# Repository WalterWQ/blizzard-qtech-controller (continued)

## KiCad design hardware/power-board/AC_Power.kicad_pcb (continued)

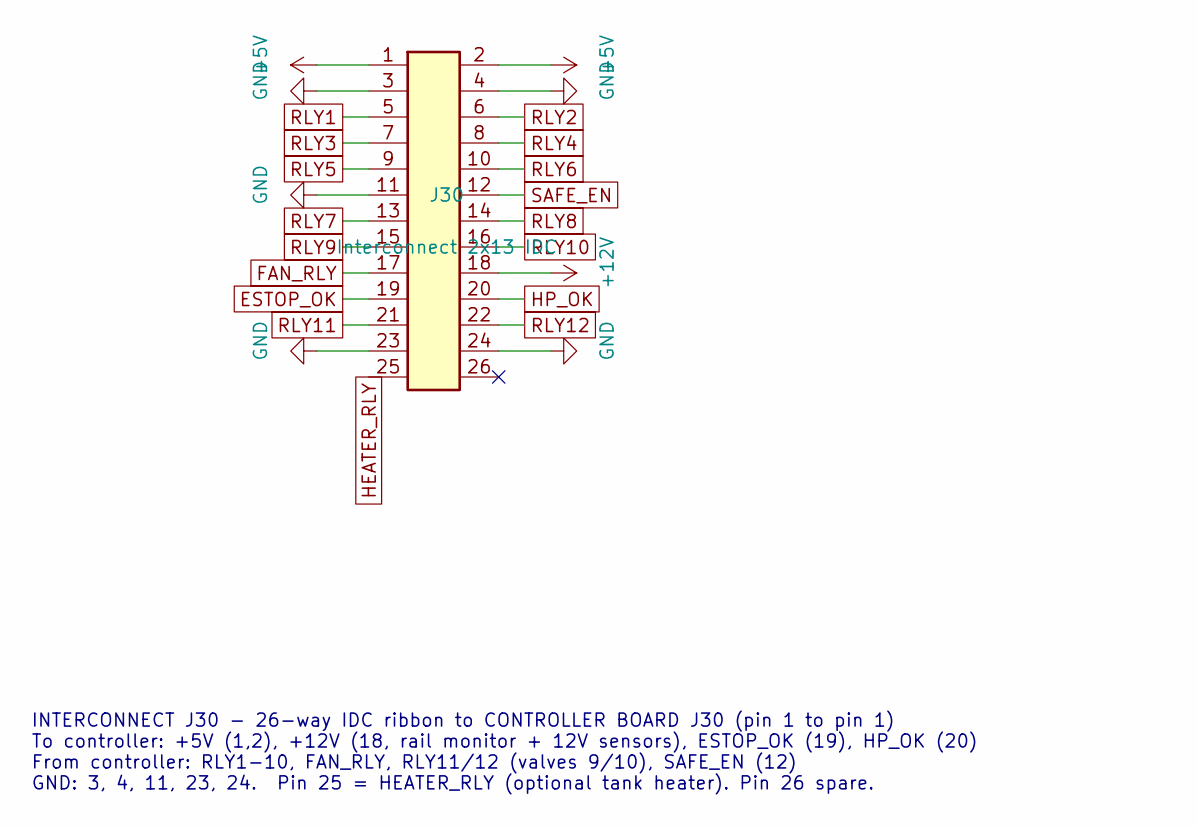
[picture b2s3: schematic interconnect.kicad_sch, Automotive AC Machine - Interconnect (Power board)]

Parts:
J30: Interconnect 2x13 IDC; IDC-Header_2x13_P2.54mm_Vertical

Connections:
+5V: J30.1, J30.2; also elsewhere on the board
+12V: J30.18; also elsewhere on the board
ESTOP_OK: J30.19; also elsewhere on the board
FAN_RLY: J30.17; also elsewhere on the board
GND: J30.3, J30.4, J30.11, J30.23, J30.24; also elsewhere on the board
HEATER_RLY: J30.25; also elsewhere on the board
HP_OK: J30.20; also elsewhere on the board
N_J30.26: J30.26
RLY1: J30.5; also elsewhere on the board
RLY2: J30.6; also elsewhere on the board
RLY3: J30.7; also elsewhere on the board
RLY4: J30.8; also elsewhere on the board
RLY5: J30.9; also elsewhere on the board
RLY6: J30.10; also elsewhere on the board
RLY7: J30.13; also elsewhere on the board
RLY8: J30.14; also elsewhere on the board
RLY9: J30.15; also elsewhere on the board
RLY10: J30.16; also elsewhere on the board
RLY11: J30.21; also elsewhere on the board
RLY12: J30.22; also elsewhere on the board
SAFE_EN: J30.12; also elsewhere on the board

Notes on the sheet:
INTERCONNECT J30 - 26-way IDC ribbon to CONTROLLER BOARD J30 (pin 1 to pin 1) To controller: +5V (1,2), +12V (18, rail monitor + 12V sensors), ESTOP_OK (19), HP_OK (20) From controller: RLY1-10, FAN_RLY, RLY11/12 (valves 9/10), SAFE_EN (12) GND: 3, 4, 11, 23, 24. Pin 25 = HEATER_RLY (optional tank 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

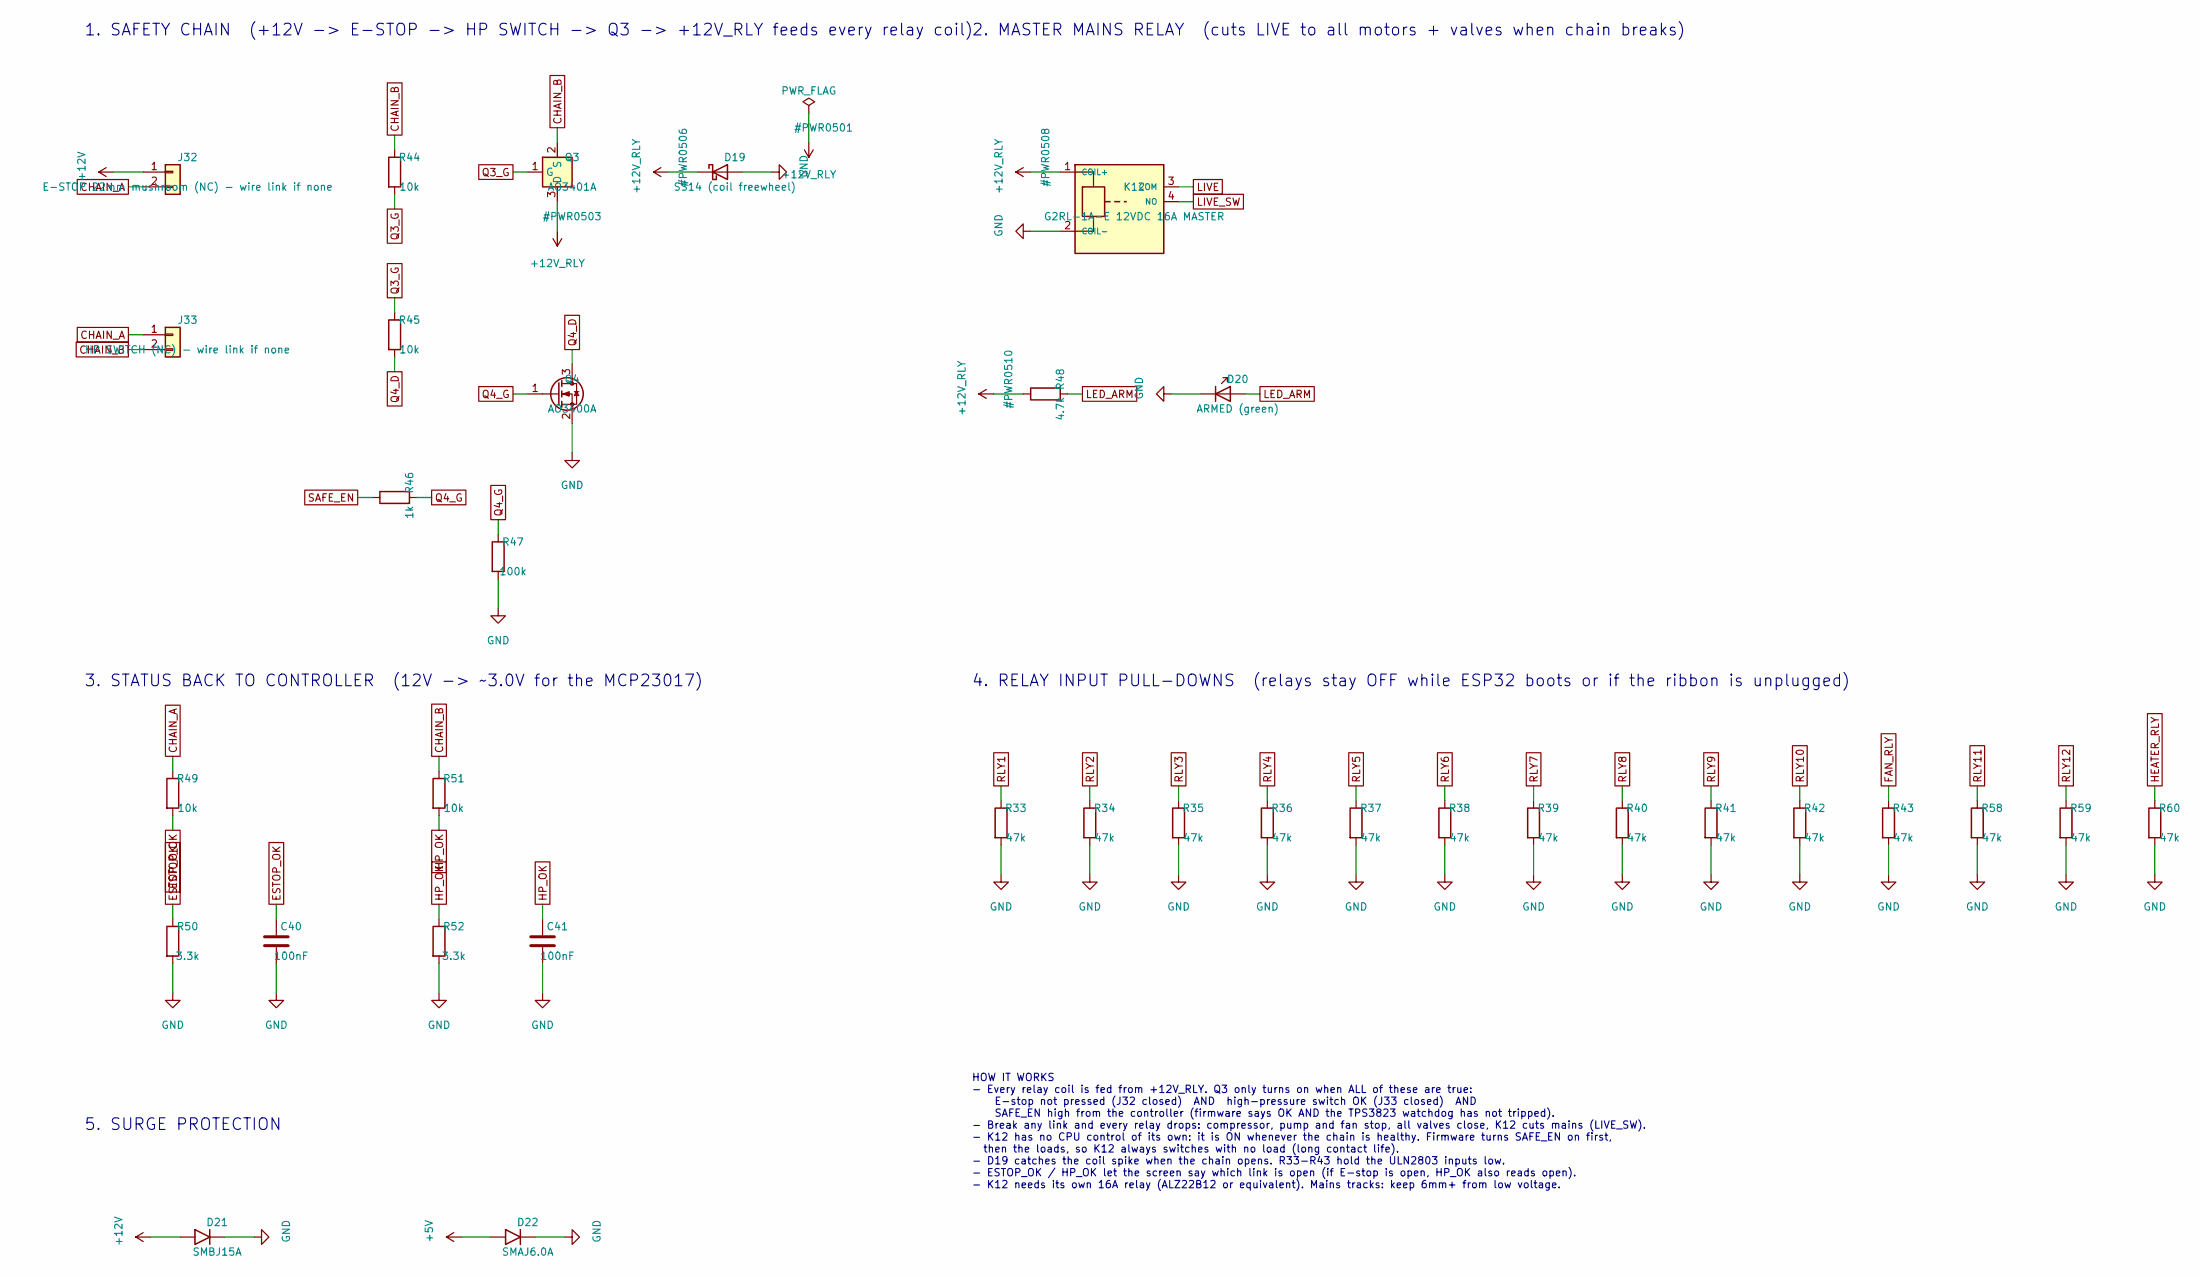
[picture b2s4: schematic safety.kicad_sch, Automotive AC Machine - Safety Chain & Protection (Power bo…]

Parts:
C40, C41: 100nF; C_0805_2012Metric
D19: SS14 (coil freewheel); D_SMA
D20: ARMED (green); LED_0805_2012Metric
D21: SMBJ15A; D_SMB
D22: SMAJ6.0A; D_SMA
J32: E-STOP 22mm mushroom (NC) - wire link if none; TerminalBlock_Phoenix_MKDS-1,5-2-5.08_1x02_P5.08mm_Horizont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
J33: HP SWITCH (NC) - wire link if none; TerminalBlock_Phoenix_MKDS-1,5-2-5.08_1x02_P5.08mm_Horizont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
K12: G2RL-1A-E 12VDC 16A MASTER; Relay_G2RL-1A-E_QT
Q3: AO3401A; SOT-23
Q4: AO3400A; SOT-23
R33, R34, R35, R36, R37, R38, R39, R40, R41, R42, R43, R58, R59, R60: 47k; R_0805_2012Metric
R44, R45, R49, R51: 10k; R_0805_2012Metric
R46: 1k; R_0805_2012Metric
R47: 100k; R_0805_2012Metric
R48: 4.7k; R_0805_2012Metric
R50, R52: 3.3k; R_0805_2012Metric

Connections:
+5V: D22.1 (K); also elsewhere on the board
+12V: D21.1 (K), J32.1; also elsewhere on the board
+12V_RLY: D19.1 (K), K12.1 (COIL+), Q3.3 (D), R48.1; also elsewhere on the board
CHAIN_A: J32.2, J33.1, R49.1
CHAIN_B: J33.2, Q3.2 (S), R44.1, R51.1
ESTOP_OK: C40.1, R49.2, R50.1; also elsewhere on the board
FAN_RLY: R43.1; also elsewhere on the board
GND: C40.2, C41.2, D19.2 (A), D20.1 (K), D21.2 (A), D22.2 (A), K12.2 (COIL-), Q4.2 (S), R33.2, R34.2, R35.2, R36.2, R37.2, R38.2, R39.2, R40.2, R41.2, R42.2, R43.2, R47.2, R50.2, R52.2, R58.2, R59.2, R60.2; also elsewhere on the board
HEATER_RLY: R60.1; also elsewhere on the board
HP_OK: C41.1, R51.2, R52.1; also elsewhere on the board
LED_ARM: D20.2 (A), R48.2
LIVE: K12.3 (COM); also elsewhere on the board
LIVE_SW: K12.4 (NO); also elsewhere on the board
Q3_G: Q3.1 (G), R44.2, R45.1
Q4_D: Q4.3 (D), R45.2
Q4_G: Q4.1 (G), R46.2, R47.1
RLY1: R33.1; also elsewhere on the board
RLY2: R34.1; also elsewhere on the board
RLY3: R35.1; also elsewhere on the board
RLY4: R36.1; also elsewhere on the board
RLY5: R37.1; also elsewhere on the board
RLY6: R38.1; also elsewhere on the board
RLY7: R39.1; also elsewhere on the board
RLY8: R40.1; also elsewhere on the board
RLY9: R41.1; also elsewhere on the board
RLY10: R42.1; also elsewhere on the board
RLY11: R58.1; also elsewhere on the board
RLY12: R59.1; also elsewhere on the board
SAFE_EN: R46.1; also elsewhere on the board

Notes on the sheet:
1. SAFETY CHAIN (+12V -> E-STOP -> HP SWITCH -> Q3 -> +12V_RLY feeds every relay coil)
2. MASTER MAINS RELAY (cuts LIVE to all motors + valves when chain breaks)
3. STATUS BACK TO CONTROLLER (12V -> ~3.0V for the MCP23017)
4. RELAY INPUT PULL-DOWNS (relays stay OFF while ESP32 boots or if the ribbon is unplugged)
5. SURGE PROTECTION
HOW IT WORKS - Every relay coil is fed from +12V_RLY. Q3 only turns on when ALL of these are true: E-stop not pressed (J32 closed) AND high-pressure switch OK (J33 closed) AND SAFE_EN high from the controller (firmware says OK AND the TPS3823 watchdog has not tripped). - Break any link and every re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

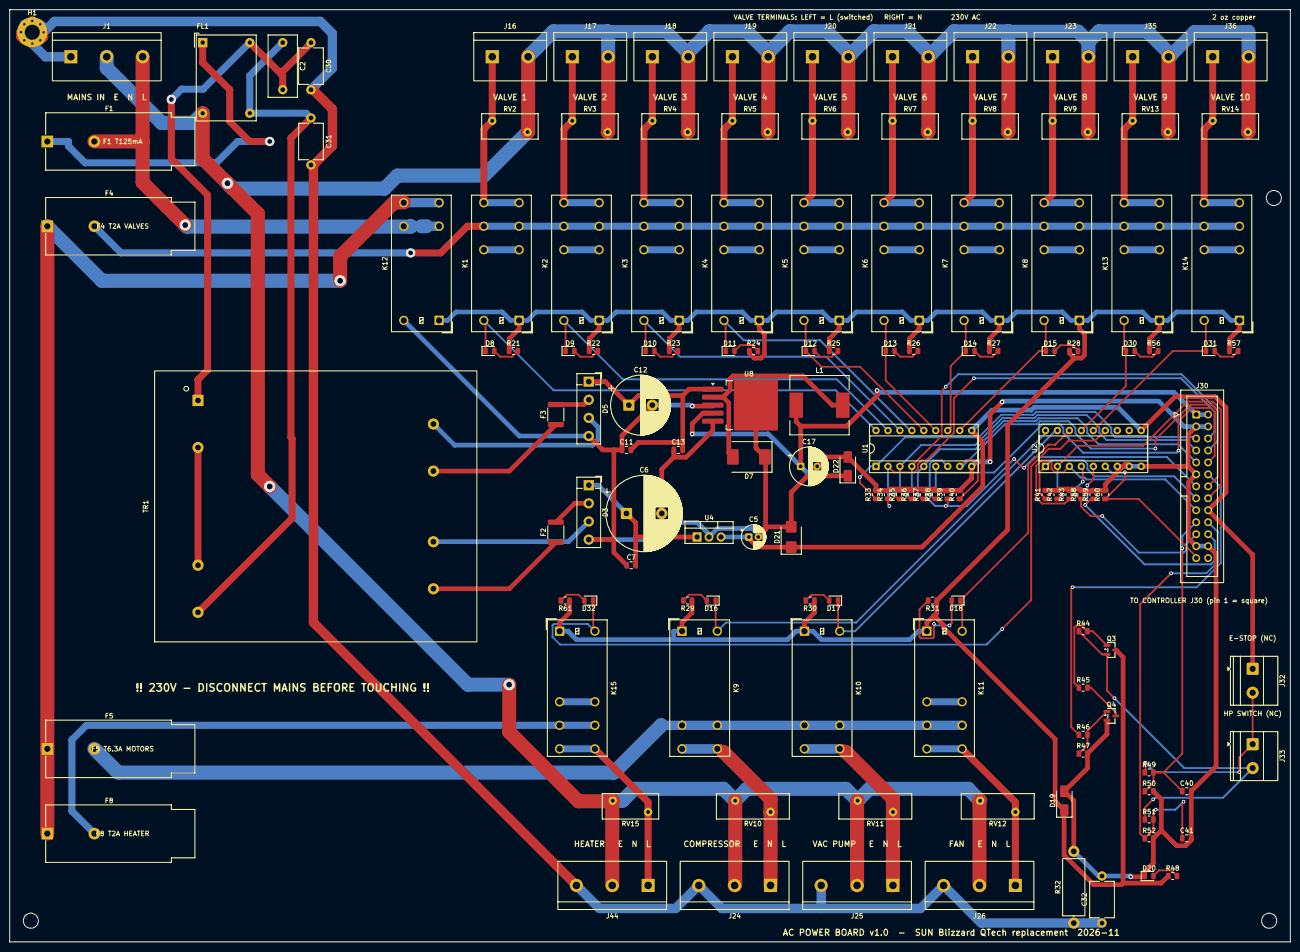
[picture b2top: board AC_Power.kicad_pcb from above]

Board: 2 copper layers, 272.0 x 198.0 mm, 138 parts (0 on the bottom side), 89 nets.

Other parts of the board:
H2, H3, H4: M3; MountingHole_3.2mm_M3

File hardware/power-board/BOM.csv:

Line,Qty per board,Part to buy,Package,What it is,References,Notes
1,2,ULN2803A,DIP-18 (socket),8-way relay driver,"U1, U2",Fit in an 18-pin DIP socket
2,1,LM2937ET-12,TO-220,12V linear regulator,U4,Needs a small TO-220 heatsink
3,1,LM2596S-5.0,TO-263-5,5V buck regulator,U8,
4,1,AO3401A,SOT-23,P-channel MOSFET,Q3,
5,1,AO3400A,SOT-23,N-channel MOSFET,Q4,
6,11,Omron G2RL-1-E DC12,G2RL 5-pin (SPDT),"12A changeover relay, 12V coil","K1, K2, K3, K4, K5, K6, K7, K8, K11, K13, K14","K1-K8, K13, K14 valves; K11 condenser fan"
7,3,Omron G2RL-1A-E DC12,G2RL 4-pin (SPST-NO),"16A relay, 12V coil","K9, K10, K12","K9 compressor, K10 vacuum pump, K12 master"
8,1,Omron G2RL-1-E DC12,G2RL 5-pin (SPDT),"12A changeover relay, 12V coil",K15,Optional: only fit if the machine has a tank heater
9,2,KBP206G,"KBP (in-line, 4-pin)",2A 600V bridge rectifier,"D3, D5",
10,1,SS54,SMC,5A Schottky diode,D7,
11,13,0805 LED (any colour),0805 LED,Indicator LED,"D8, D9, D10, D11, D12, D13, D14, D15, D16, D17, D18, D30, D31",
12,1,SS14,SMA,1A Schottky diode,D19,
13,1,"0805 LED, green",0805 LED,Indicator LED,D20,
14,1,SMBJ15A,SMB,"TVS diode, 12V rail",D21,
15,1,SMAJ6.0A,SMA,"TVS diode, 5V rail",D22,
16,1,0805 LED (any colour),0805 LED,Indicator LED,D32,Optional: only fit if the machine has a tank heater
17,14,4.7k 1% 0805,0805,Resistor,"R21, R22, R23, R24, R25, R26, R27, R28, R29, R30, R31, R48, R56, R57",
18,1,"1M 1/2W 1% Axial, 15.24mm pitch","Axial, 15.24mm pitch",Resistor,R32,
19,14,47k 1% 0805,0805,Resistor,"R33, R34, R35, R36, R37, R38, R39, R40, R41, R42, R43, R58, R59, R60",
20,4,10k 1% 0805,0805,Resistor,"R44, R45, R49, R51",
21,1,1k 1% 0805,0805,Resistor,R46,
22,1,100k 1% 0805,0805,Resistor,R47,
23,2,3.3k 1% 0805,0805,Resistor,"R50, R52",
24,1,4.7k 1% 0805,0805,Resistor,R61,Optional: only fit if the machine has a tank heater
25,10,TDK/EPCOS S10K275,12mm disc,Mains varistor (valve outputs),"RV2, RV3, RV4, RV5, RV6, RV7, RV8, RV9, RV13, RV14",
26,3,TDK/EPCOS S14K275,15.5mm disc,Mains varistor (motor outputs),"RV10, RV11, RV12",
27,1,TDK/EPCOS S10K275,12mm disc,Mains varistor (valve outputs),RV15,Optional: only fit if the machine has a tank heater
28,1,100nF X2 275VAC,"Box, 10mm pitch (13 x 6mm)",Mains safety capacitor,C2,
29,1,22uF 25V electrolytic,"Radial 5mm, 2mm pitch",Capacitor,C5,
30,1,2200uF 35V electrolytic,"Radial 16mm, 7.5mm pitch",Capacitor,C6,
31,5,100nF X7R 0805,0805,Capacitor,"C7, C11, C13, C40, C41",
32,1,1000uF 35V electrolytic,"Radial 12.5mm, 5mm pitch",Capacitor,C12,
33,1,220uF 16V electrolytic,"Radial 8mm, 3.5mm pitch",Capacitor,C17,
34,2,2.2nF Y2 300VAC,"Disc, 10mm pitch",Mains safety capacitor,"C30, C31",
35,1,4.7nF Y2 300VAC,"Disc, 10mm pitch",Mains safety capacitor,C32,
36,1,Bourns SRR1260-470M (or equiv.),12x12mm SMD,Buck regulator inductor,L1,
37,1,Schurter FAB 0031-355x (5x20mm) + fuse T125mA,5x20mm fuse holder,Fuse holder,F1,
38,2,Bourns MF-MSMF110 (1.1A hold),1812,Resettable fuse,"F2, F3",
39,1,Schurter FAB 0031-355x (5x20mm) + fuse T2A,5x20mm fuse holder,Fuse holder,F4,
40,1,Schurter FAB 0031-355x (5x20mm) + fuse T6.3A,5x20mm fuse holder,Fuse holder,F5,
41,1,Schurter FAB 0031-355x (5x20mm) + fuse T2A,5x20mm fuse holder,Fuse holder,F8,Optional: only fit if the machine has a tank heater
42,1,"KF7.62-3P (7.62mm pitch, 3-way)",7.62mm screw terminal,Mains screw terminal,J1,"Mains in: E, N, L"
43,10,"KF7.62-2P (7.62mm pitch, 2-way)",7.62mm screw terminal,Mains screw terminal,"J16, J17, J18, J19, J20, J21, J22, J23, J35, J36",Valve coils VALVE1-10
44,3,"KF7.62-3P (7.62mm pitch, 3-way)",7.62mm screw terminal,Mains screw terminal,"J24, J25, J26","Compressor, vacuum pump, condenser fan. Pin order E, N, L"
45,1,"2x13 (26-way) box header, 2.54mm",2.54mm box header,Ribbon header,J30,Labels: Interconnect 2x13 IDC
46,1,"KF7.62-3P (7.62mm pitch, 3-way)",7.62mm screw terminal,Mains screw terminal,J44,"Optional: tank heater. Pin order E, N, L"
47,1,Hahn BV UI 395 0091,PCB transformer,Mains PCB transformer,TR1,Reuse the one from the old board. Check pin spacing before ordering the PCB
48,1,Schaffner RN212-1.2-02,Schaffner RN212 (12.5 x 18mm),Mains EMI filter choke,FL1,
49,2,"KF2EDG 5.08mm 2-way (or Phoenix MKDS 1,5/2-5,08)",5.08mm screw terminal,Low-voltage screw terminal,"J32, J33",E-stop (NC) and HP switch (NC). Wire a link across if not used
Total,,Total parts placed per board / parts to buy,,,,

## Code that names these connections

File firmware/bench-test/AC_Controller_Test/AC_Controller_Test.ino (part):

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// ------------------------------------------------------------ pin map (from the PCB)
#define PIN_SDA        1
#define PIN_SCL        2
#define PIN_SAFE_GPIO  3      // AND-ed with watchdog -> SAFE_EN (J30 pin 12)
#define PIN_BOOT       0      // SW1
#define PIN_LCD_RS     10
#define PIN_LCD_E      11
#define PIN_LCD_D4     12
#define PIN_LCD_D5     13
#define PIN_LCD_D6     14
#define PIN_LCD_D7     21
#define PIN_LCD_BL     38     // backlight MOSFET Q2, HIGH = on
#define PIN_PRN_TX     39
#define PIN_KEY_INT    40
#define PIN_BUZZER     41     // buzzer MOSFET Q1, HIGH = on
#define PIN_WDT        42     // TPS3823 WDI - must toggle at least every ~1 s
#define PIN_PRN_RX     47
#define PIN_RGB        48     // WS2812B

#define LCD_COLS 16           // change to 20 if your display is 20 characters wide

// ------------------------------------------------------------ I2C addresses
#define A_MCP_KEYS   0x20     // U3  keypad, heater, fan, E-stop, HP switch, printer busy
#define A_MCP_EXP    0x21     // U19 RLY11, RLY12, J43 expansion
#define A_NAU        0x2A     // U15 load cell
#define A_ADS1       0x48     // U9  tank NTC, P1, P2, P3
#define A_ADS2       0x49     // U13 CT pump, CT comp, 12V monitor, 5V monitor
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void wdtTask(void *) {
  bool s = false;
  for (;;) {
    if (wdtFeed) { s = !s; digitalWrite(PIN_WDT, s); }
    vTaskDelay(pdMS_TO_TICKS(100));
  }
}
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
// ------------------------------------------------------------ LCD (HD44780, 4-bit, write only)
void lcdNib(uint8_t n) {
  digitalWrite(PIN_LCD_D4, n & 1); digitalWrite(PIN_LCD_D5, (n >> 1) & 1);
  digitalWrite(PIN_LCD_D6, (n >> 2) & 1); digitalWrite(PIN_LCD_D7, (n >> 3) & 1);
  digitalWrite(PIN_LCD_E, HIGH); delayMicroseconds(2);
  digitalWrite(PIN_LCD_E, LOW);  delayMicroseconds(60);
}
void lcdByte(uint8_t b, bool data) {
  digitalWrite(PIN_LCD_RS, data); lcdNib(b >> 4); lcdNib(b & 0x0F);
}
void lcdCmd(uint8_t c) { lcdByte(c, false); if (c < 4) delay(3); }
void lcdInit() {
  int p[] = {PIN_LCD_RS, PIN_LCD_E, PIN_LCD_D4, PIN_LCD_D5, PIN_LCD_D6, PIN_LCD_D7};
  for (int i : p) { pinMode(i, OUTPUT); digitalWrite(i, LOW); }
  delay(60);
  lcdNib(3); delay(5); lcdNib(3); delayMicroseconds(150); lcdNib(3); lcdNib(2);
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    String k = keyScan();
    if (k != last && k != "") {
      Serial.println("  key: " + k); lcdLine(1, k.c_str());
      digitalWrite(PIN_BUZZER, HIGH); delay(30); digitalWrite(PIN_BUZZER, LOW);
    }
    last = k; delay(30);
  }
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
void outputsTest() {
  Serial.println("Backlight off/on, buzzer beep, RGB LED red/green/blue.");
  digitalWrite(PIN_LCD_BL, LOW); delay(700); digitalWrite(PIN_LCD_BL, HIGH);
  digitalWrite(PIN_BUZZER, HIGH); delay(300); digitalWrite(PIN_BUZZER, LOW);
  rgb(80, 0, 0); delay(600); rgb(0, 80, 0); delay(600); rgb(0, 0, 80); delay(600); rgb(0, 0, 0);
  Serial.println("Did you see/hear all of them? (backlight blink, beep, red, green, blue)");
}

void watchdogTest() {
  Serial.println("Measure J30 pin 12 (SAFE_EN) to GND, or put an LED + 1k on it.");
  Serial.println("Step 1: SAFE_EN ON for 5 s  -> should read about 3.3 V");
  digitalWrite(PIN_SAFE_GPIO, HIGH); delay(5000);
  Serial.println("Step 2: SAFE_EN OFF for 3 s -> should read 0 V");
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  Serial.println("Printer loopback:");
  Serial.println("  RS-232: J5 jumper on pins 1-2, bridge J7 pin 3 to J7 pin 5");
  Serial.println("  TTL   : J5 jumper on pins 2-3, bridge J4 pin 2 to J4 pin 3");
  Serial1.begin(9600, SERIAL_8N1, PIN_PRN_RX, PIN_PRN_TX);
  delay(50); while (Serial1.available()) Serial1.read();
  const char *msg = "LOOPBACK-123";
  Serial1.print(msg); Serial1.flush(); delay(100);
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
// ------------------------------------------------------------ setup / loop
void setup() {
  pinMode(PIN_WDT, OUTPUT);
  xTaskCreate(wdtTask, "wdt", 2048, nullptr, 5, nullptr);   // feed the watchdog straight away

  pinMode(PIN_SAFE_GPIO, OUTPUT); digitalWrite(PIN_SAFE_GPIO, LOW);
  for (int i = 0; i < NOUTS; i++) if (OUTS[i].kind == 0) { pinMode(OUTS[i].pin, OUTPUT); digitalWrite(OUTS[i].pin, LOW); }
  pinMode(PIN_BUZZER, OUTPUT); digitalWrite(PIN_BUZZER, LOW);
  pinMode(PIN_LCD_BL, OUTPUT); digitalWrite(PIN_LCD_BL, HIGH);
  pinMode(PIN_BOOT, INPUT_PULLUP);
  pinMode(PIN_KEY_INT, INPUT_PULLUP);
  rgb(0, 0, 0);

  Serial.begin(115200);
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      f = 0; framWrite(F_WDTFLAG, &f, 1);
    }
  }
  digitalWrite(PIN_BUZZER, HIGH); delay(80); digitalWrite(PIN_BUZZER, LOW);
  delay(800);
  runAuto();
  menu();
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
